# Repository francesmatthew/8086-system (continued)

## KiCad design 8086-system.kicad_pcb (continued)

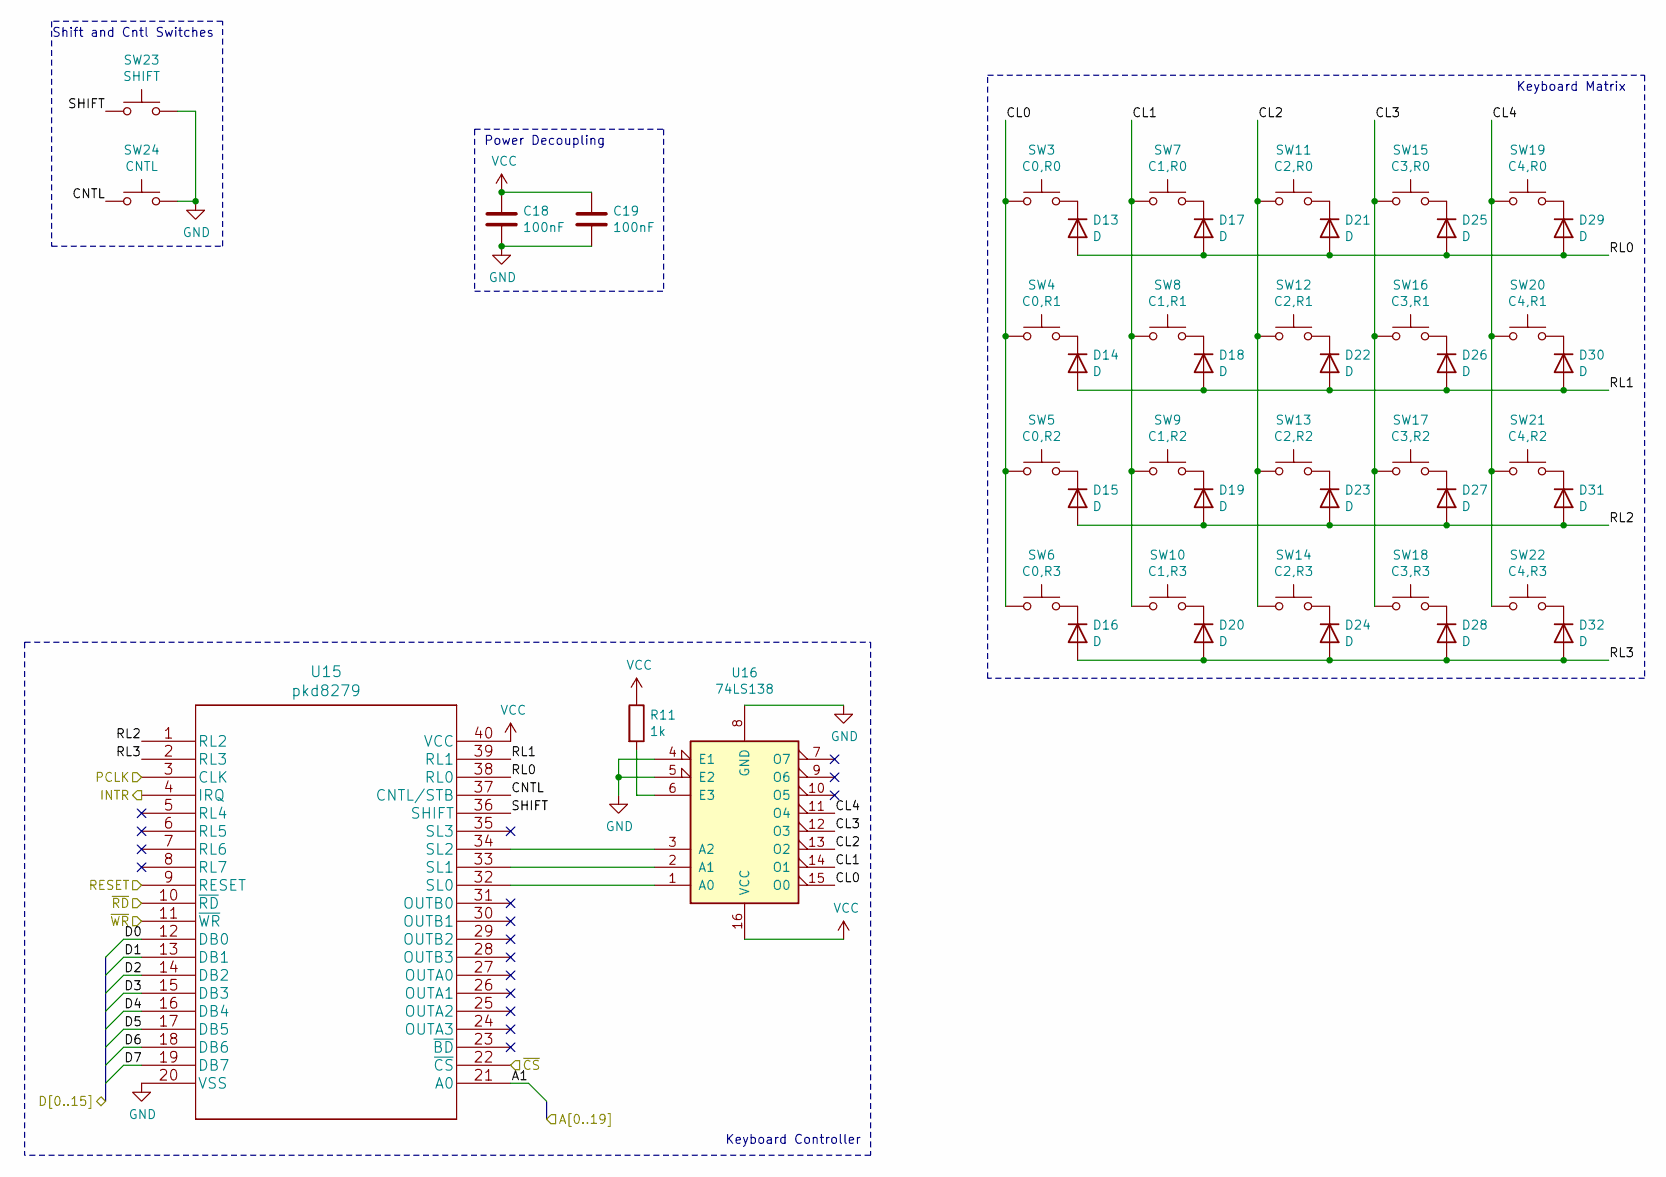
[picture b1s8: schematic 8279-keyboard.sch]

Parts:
C18, C19: 100nF; C_Rect_L4.0mm_W2.5mm_P2.50mm
D13, D14, D15, D16, D17, D18, D19, D20, D21, D22, D23, D24, D25, D26, D27, D28, D29, D30, D31, D32: D; D_DO-35_SOD27_P7.62mm_Horizontal
R11: 1k; R_Axial_DIN0207_L6.3mm_D2.5mm_P10.16mm_Horizontal
SW3: C0,R0; SW_Cherry_MX_1.00u_PCB
SW4: C0,R1; SW_Cherry_MX_1.00u_PCB
SW5: C0,R2; SW_Cherry_MX_1.00u_PCB
SW6: C0,R3; SW_Cherry_MX_1.00u_PCB
SW7: C1,R0; SW_Cherry_MX_1.00u_PCB
SW8: C1,R1; SW_Cherry_MX_1.00u_PCB
SW9: C1,R2; SW_Cherry_MX_1.00u_PCB
SW10: C1,R3; SW_Cherry_MX_1.00u_PCB
SW11: C2,R0; SW_Cherry_MX_1.00u_PCB
SW12: C2,R1; SW_Cherry_MX_1.00u_PCB
SW13: C2,R2; SW_Cherry_MX_1.00u_PCB
SW14: C2,R3; SW_Cherry_MX_1.00u_PCB
SW15: C3,R0; SW_Cherry_MX_1.00u_PCB
SW16: C3,R1; SW_Cherry_MX_1.00u_PCB
SW17: C3,R2; SW_Cherry_MX_1.00u_PCB
SW18: C3,R3; SW_Cherry_MX_1.00u_PCB
SW19: C4,R0; SW_Cherry_MX_1.00u_PCB
SW20: C4,R1; SW_Cherry_MX_1.00u_PCB
SW21: C4,R2; SW_Cherry_MX_1.00u_PCB
SW22: C4,R3; SW_Cherry_MX_1.00u_PCB
SW23: SHIFT; SW_Cherry_MX_1.00u_PCB
SW24: CNTL; SW_Cherry_MX_1.00u_PCB
U15: pkd8279
U16: 74LS138; DIP-16_W7.62mm

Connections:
/8086-processor/A1: U15.21 (A0); also elsewhere on the board
/8086-processor/D0: U15.12 (DB0); also elsewhere on the board
/8086-processor/D1: U15.13 (DB1); also elsewhere on the board
/8086-processor/D2: U15.14 (DB2); also elsewhere on the board
/8086-processor/D3: U15.15 (DB3); also elsewhere on the board
/8086-processor/D4: U15.16 (DB4); also elsewhere on the board
/8086-processor/D5: U15.17 (DB5); also elsewhere on the board
/8086-processor/D6: U15.18 (DB6); also elsewhere on the board
/8086-processor/D7: U15.19 (DB7); also elsewhere on the board
/8279-keyboard/CL0: SW3.1, SW4.1, SW5.1, SW6.1, U16.15 (O0)
/8279-keyboard/CL1: SW7.1, SW8.1, SW9.1, SW10.1, U16.14 (O1)
/8279-keyboard/CL2: SW11.1, SW12.1, SW13.1, SW14.1, U16.13 (O2)
/8279-keyboard/CL3: SW15.1, SW16.1, SW17.1, SW18.1, U16.12 (O3)
/8279-keyboard/CL4: SW19.1, SW20.1, SW21.1, SW22.1, U16.11 (O4)
/8279-keyboard/CNTL: SW24.1, U15.37 (CNTL/STB)
/8279-keyboard/RL0: D13.2 (A), D17.2 (A), D21.2 (A), D25.2 (A), D29.2 (A), U15.38 (RL0)
/8279-keyboard/RL1: D14.2 (A), D18.2 (A), D22.2 (A), D26.2 (A), D30.2 (A), U15.39 (RL1)
/8279-keyboard/RL2: D15.2 (A), D19.2 (A), D23.2 (A), D27.2 (A), D31.2 (A), U15.1 (RL2)
/8279-keyboard/RL3: D16.2 (A), D20.2 (A), D24.2 (A), D28.2 (A), D32.2 (A), U15.2 (RL3)
/8279-keyboard/SHIFT: SW23.1, U15.36 (SHIFT)
/KEYBOARD_INTR: U15.4 (IRQ); also elsewhere on the board
/PCLK: U15.3 (CLK); also elsewhere on the board
/RESET: U15.9 (RESET); also elsewhere on the board
/~CS_KEYBOARD: U15.22 (~CS); also elsewhere on the board
/~RD: U15.10 (~RD); also elsewhere on the board
/~WR: U15.11 (~WR); also elsewhere on the board
GND: C18.2, C19.2, SW23.2, SW24.2, U15.20 (VSS), U16.4 (E1), U16.5 (E2), U16.8 (GND); also elsewhere on the board
unnamed: D13.1 (K), SW3.2
unnamed: D14.1 (K), SW4.2
unnamed: D15.1 (K), SW5.2
unnamed: D16.1 (K), SW6.2
unnamed: D17.1 (K), SW7.2
unnamed: D18.1 (K), SW8.2
unnamed: D19.1 (K), SW9.2
unnamed: D20.1 (K), SW10.2
unnamed: D21.1 (K), SW11.2
unnamed: D22.1 (K), SW12.2
unnamed: D23.1 (K), SW13.2
unnamed: D24.1 (K), SW14.2
unnamed: D25.1 (K), SW15.2
unnamed: D26.1 (K), SW16.2
unnamed: D27.1 (K), SW17.2
unnamed: D28.1 (K), SW18.2
unnamed: D29.1 (K), SW19.2
unnamed: D30.1 (K), SW20.2
unnamed: D31.1 (K), SW21.2
unnamed: D32.1 (K), SW22.2
unnamed: R11.2, U16.6 (E3)
unnamed: U15.32 (SL0), U16.1 (A0)
unnamed: U15.33 (SL1), U16.2 (A1)
unnamed: U15.34 (SL2), U16.3 (A2)
VCC: C18.1, C19.1, R11.1, U15.40 (VCC), U16.16 (VCC); also elsewhere on the board

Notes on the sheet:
Keyboard Matrix
Keyboard Controller
Shift and Cntl Switches
Power Decoupling

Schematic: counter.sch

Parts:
C20: 100nF; C_Rect_L4.0mm_W2.5mm_P2.50mm
J17: Counter0; PinHeader_1x03_P2.54mm_Vertical
J18: Counter1; PinHeader_1x03_P2.54mm_Vertical
J19: Counter2; PinHeader_1x03_P2.54mm_Vertical
R12, R13, R14, R15, R16, R17: 1k; R_Axial_DIN0207_L6.3mm_D2.5mm_P10.16mm_Horizontal
U17: 8254; DIP-24_W15.24mm

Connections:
/8086-processor/A1: U17.19 (A0); also elsewhere on the board
/8086-processor/A2: U17.20 (A1); also elsewhere on the board
/8086-processor/D0: U17.8 (D0); also elsewhere on the board
/8086-processor/D1: U17.7 (D1); also elsewhere on the board
/8086-processor/D2: U17.6 (D2); also elsewhere on the board
/8086-processor/D3: U17.5 (D3); also elsewhere on the board
/8086-processor/D4: U17.4 (D4); also elsewhere on the board
/8086-processor/D5: U17.3 (D5); also elsewhere on the board
/8086-processor/D6: U17.2 (D6); also elsewhere on the board
/8086-processor/D7: U17.1 (D7); also elsewhere on the board
/COUNTER_INTR: U17.13 (OUT1); also elsewhere on the board
/~CS_COUNTER: U17.21 (~CS~); also elsewhere on the board
/~RD: U17.22 (~RD~); also elsewhere on the board
/~WR: U17.23 (~WR~); also elsewhere on the board
GND: C20.2, J18.3, R12.2, R13.2, R14.2, R15.2, R16.2, R17.2, U17.12 (GND); also elsewhere on the board
unnamed: J17.1, R12.1, U17.9 (CLK0)
unnamed: J17.2, R13.1, U17.11 (G0)
unnamed: J17.3, U17.10 (OUT0)
unnamed: J18.1, R14.1, U17.15 (CLK1)
unnamed: J18.2, R15.1, U17.14 (G1)
unnamed: J19.1, R16.1, U17.18 (CLK2)
unnamed: J19.2, R17.1, U17.16 (G2)
unnamed: J19.3, U17.17 (OUT2)
VCC: C20.1, U17.24 (VCC); also elsewhere on the board

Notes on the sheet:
8254 Interval Timer
Power decoupling

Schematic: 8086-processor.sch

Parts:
C21, C22, C23, C24, C25, C26, C27, C28: 100nF; C_Rect_L4.0mm_W2.5mm_P2.50mm
D3: 1N4148; D_DO-35_SOD27_P7.62mm_Horizontal
R18, R20: 1k; R_Axial_DIN0207_L6.3mm_D2.5mm_P10.16mm_Horizontal
R19: 10k; R_Axial_DIN0207_L6.3mm_D2.5mm_P10.16mm_Horizontal
SW25: NMI; SW_Cherry_MX_1.00u_PCB
U18: 8086_Min_Mode; DIP-40_W15.24mm
U19, U21, U22: 74LS374; DIP-20_W7.62mm
U20: 74LS244; DIP-20_W7.62mm
U23, U24: 74LS245; DIP-20_W7.62mm

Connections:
/8086-processor/A0: U19.9 (O3); also elsewhere on the board
/8086-processor/A1: U19.6 (O2); also elsewhere on the board
/8086-processor/A2: U19.5 (O1); also elsewhere on the board
/8086-processor/A3: U19.2 (O0); also elsewhere on the board
/8086-processor/A4: U19.12 (O4); also elsewhere on the board
/8086-processor/A5: U19.15 (O5); also elsewhere on the board
/8086-processor/A6: U19.16 (O6); also elsewhere on the board
/8086-processor/A7: U19.19 (O7); also elsewhere on the board
/8086-processor/A8: U21.9 (O3); also elsewhere on the board
/8086-processor/A9: U21.6 (O2); also elsewhere on the board
/8086-processor/A10: U21.5 (O1); also elsewhere on the board
/8086-processor/A11: U21.2 (O0); also elsewhere on the board
/8086-processor/A12: U21.12 (O4); also elsewhere on the board
/8086-processor/A13: U21.15 (O5); also elsewhere on the board
/8086-processor/A14: U21.16 (O6); also elsewhere on the board
/8086-processor/A15: U21.19 (O7); also elsewhere on the board
/8086-processor/A16: U22.2 (O0); also elsewhere on the board
/8086-processor/A17: U22.5 (O1); also elsewhere on the board
/8086-processor/A18: U22.6 (O2); also elsewhere on the board
/8086-processor/A19: U22.9 (O3); also elsewhere on the board
/8086-processor/ALE: U18.25 (ALE), U19.11 (Cp), U21.11 (Cp), U22.11 (Cp)
/8086-processor/D0: U23.18 (B0); also elsewhere on the board
/8086-processor/D1: U23.17 (B1); also elsewhere on the board
/8086-processor/D2: U23.16 (B2); also elsewhere on the board
/8086-processor/D3: U23.15 (B3); also elsewhere on the board
/8086-processor/D4: U23.14 (B4); also elsewhere on the board
/8086-processor/D5: U23.13 (B5); also elsewhere on the board
/8086-processor/D6: U23.12 (B6); also elsewhere on the board
/8086-processor/D7: U23.11 (B7); also elsewhere on the board
/8086-processor/D8: U24.18 (B0); also elsewhere on the board
/8086-processor/D9: U24.17 (B1); also elsewhere on the board
/8086-processor/D10: U24.16 (B2); also elsewhere on the board
/8086-processor/D11: U24.15 (B3); also elsewhere on the board
/8086-processor/D12: U24.14 (B4); also elsewhere on the board
/8086-processor/D13: U24.13 (B5); also elsewhere on the board
/8086-processor/D14: U24.12 (B6); also elsewhere on the board
/8086-processor/D15: U24.11 (B7); also elsewhere on the board
/8086-processor/DT\~R: U18.27 (DT/~R~), U23.1 (A->B), U24.1 (A->B)
/8086-processor/NMI: U18.17 (NMI), U20.12 (O3a)
/8086-processor/~DEN: U18.26 (~DEN~), U23.19 (CE), U24.19 (CE)
/CLK: U18.19 (CLK); also elsewhere on the board
/INTR: U18.18 (INTR); also elsewhere on the board
/M\~IO: U20.18 (O0a); also elsewhere on the board
/READY: U18.22 (READY); also elsewhere on the board
/RESET: U18.21 (RESET); also elsewhere on the board
/~BHE: U22.12 (O4); also elsewhere on the board
/~INTA: U18.24 (~INTA~); also elsewhere on the board
/~RD: U20.14 (O2a); also elsewhere on the board
/~WR: U20.16 (O1a); also elsewhere on the board
GND: C22.1, C23.1, C24.1, C25.1, C26.1, C27.1, C28.1, R19.1, U18.1 (GND), U18.20 (GND), U18.23 (~TEST~), U18.31 (HOLD), U19.1 (OE), U19.10 (GND), U20.1 (OEa), U20.10 (GND), U20.11 (I0b), U20.13 (I1b), U20.15 (I2b), U20.17 (I3b), U20.19 (OEb), U21.1 (OE), U21.10 (GND), U22.1 (OE), U22.10 (GND), U22.14 (D5), U22.17 (D6), U22.18 (D7), U23.10 (GND), U24.10 (GND); also elsewhere on the board
unnamed: C21.2, D3.2 (A), R20.1, U20.8 (I3a)
unnamed: D3.1 (K), R19.2, R20.2, SW25.1
unnamed: R18.2, U18.33 (MN/~MX~)
unnamed: U18.2 (AD14), U21.17 (D6), U24.8 (A6)
unnamed: U18.3 (AD13), U21.14 (D5), U24.7 (A5)
unnamed: U18.4 (AD12), U21.13 (D4), U24.6 (A4)
unnamed: U18.5 (AD11), U21.3 (D0), U24.5 (A3)
unnamed: U18.6 (AD10), U21.4 (D1), U24.4 (A2)
unnamed: U18.7 (AD9), U21.7 (D2), U24.3 (A1)
unnamed: U18.8 (AD8), U21.8 (D3), U24.2 (A0)
unnamed: U18.9 (AD7), U19.18 (D7), U23.9 (A7)
unnamed: U18.10 (AD6), U19.17 (D6), U23.8 (A6)
unnamed: U18.11 (AD5), U19.14 (D5), U23.7 (A5)
unnamed: U18.12 (AD4), U19.13 (D4), U23.6 (A4)
unnamed: U18.13 (AD3), U19.3 (D0), U23.5 (A3)
unnamed: U18.14 (AD2), U19.4 (D1), U23.4 (A2)
unnamed: U18.15 (AD1), U19.7 (D2), U23.3 (A1)
unnamed: U18.16 (AD0), U19.8 (D3), U23.2 (A0)
unnamed: U18.28 (M/~IO~), U20.2 (I0a)
unnamed: U18.29 (~WR~), U20.4 (I1a)
unnamed: U18.32 (~RD~), U20.6 (I2a)
unnamed: U18.34 (~BHE~/S7), U22.13 (D4)
unnamed: U18.35 (A19/S6), U22.8 (D3)
unnamed: U18.36 (A18/S5), U22.7 (D2)
unnamed: U18.37 (A17/S4), U22.4 (D1)
unnamed: U18.38 (A16/S3), U22.3 (D0)
unnamed: U18.39 (AD15), U21.18 (D7), U24.9 (A7)
VCC: C21.1, C22.2, C23.2, C24.2, C25.2, C26.2, C27.2, C28.2, R18.1, SW25.2, U18.40 (VCC), U19.20 (VCC), U20.20 (VCC), U21.20 (VCC), U22.20 (VCC), U23.20 (VCC), U24.20 (VCC); also elsewhere on the board

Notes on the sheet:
Data Bus Transceivers
Address Bus Latches
8086 Processor
Power Decoupling
Non-Maskable Interrupt Button

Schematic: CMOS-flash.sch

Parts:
C29, C30, C31, C32, C33, C34: 100nF; C_Rect_L4.0mm_W2.5mm_P2.50mm
U25, U26: 74LS138; DIP-16_W7.62mm
U27, U28: 28F010

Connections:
+12V: C29.1, C30.1, U27.1 (VPP), U28.1 (VPP); also elsewhere on the board
/8086-processor/A0: U26.5 (E2); also elsewhere on the board
/8086-processor/A1: U27.12 (A0), U28.12 (A0); also elsewhere on the board
/8086-processor/A2: U27.11 (A1), U28.11 (A1); also elsewhere on the board
/8086-processor/A3: U27.10 (A2), U28.10 (A2); also elsewhere on the board
/8086-processor/A4: U27.9 (A3), U28.9 (A3); also elsewhere on the board
/8086-processor/A5: U27.8 (A4), U28.8 (A4); also elsewhere on the board
/8086-processor/A6: U27.7 (A5), U28.7 (A5); also elsewhere on the board
/8086-processor/A7: U27.6 (A6), U28.6 (A6); also elsewhere on the board
/8086-processor/A8: U27.5 (A7), U28.5 (A7); also elsewhere on the board
/8086-processor/A9: U27.27 (A8), U28.27 (A8); also elsewhere on the board
/8086-processor/A10: U27.26 (A9), U28.26 (A9); also elsewhere on the board
/8086-processor/A11: U27.23 (A10), U28.23 (A10); also elsewhere on the board
/8086-processor/A12: U27.25 (A11), U28.25 (A11); also elsewhere on the board
/8086-processor/A13: U27.4 (A12), U28.4 (A12); also elsewhere on the board
/8086-processor/A14: U27.28 (A13), U28.28 (A13); also elsewhere on the board
/8086-processor/A15: U27.29 (A14), U28.29 (A14); also elsewhere on the board
/8086-processor/A16: U27.3 (A15), U28.3 (A15); also elsewhere on the board
/8086-processor/A17: U27.2 (A16), U28.2 (A16); also elsewhere on the board
/8086-processor/A18: U25.1 (A0), U26.1 (A0); also elsewhere on the board
/8086-processor/A19: U25.2 (A1), U26.2 (A1); also elsewhere on the board
/8086-processor/D0: U28.13 (DQ0); also elsewhere on the board
/8086-processor/D1: U28.14 (DQ1); also elsewhere on the board
/8086-processor/D2: U28.15 (DQ2); also elsewhere on the board
/8086-processor/D3: U28.17 (DQ3); also elsewhere on the board
/8086-processor/D4: U28.18 (DQ4); also elsewhere on the board
/8086-processor/D5: U28.19 (DQ5); also elsewhere on the board
/8086-processor/D6: U28.20 (DQ6); also elsewhere on the board
/8086-processor/D7: U28.21 (DQ7); also elsewhere on the board
/8086-processor/D8: U27.13 (DQ0); also elsewhere on the board
/8086-processor/D9: U27.14 (DQ1); also elsewhere on the board
/8086-processor/D10: U27.15 (DQ2); also elsewhere on the board
/8086-processor/D11: U27.17 (DQ3); also elsewhere on the board
/8086-processor/D12: U27.18 (DQ4); also elsewhere on the board
/8086-processor/D13: U27.19 (DQ5); also elsewhere on the board
/8086-processor/D14: U27.20 (DQ6); also elsewhere on the board
/8086-processor/D15: U27.21 (DQ7); also elsewhere on the board
/CMOS-flash/~CE_HI_BYTE: U25.12 (O3), U27.22 (CE)
/CMOS-flash/~CE_LOW_BYTE: U26.12 (O3), U28.22 (CE)
/M\~IO: U25.6 (E3), U26.6 (E3); also elsewhere on the board
/~BHE: U25.5 (E2); also elsewhere on the board
/~RD: U27.24 (OE), U28.24 (OE); also elsewhere on the board
/~WR: U27.31 (WE), U28.31 (WE); also elsewhere on the board
GND: C29.2, C30.2, C31.2, C32.2, C33.2, C34.2, U25.3 (A2), U25.4 (E1), U25.8 (GND), U26.3 (A2), U26.4 (E1), U26.8 (GND), U27.16 (VSS), U28.16 (VSS); also elsewhere on the board
VCC: C31.1, C32.1, C33.1, C34.1, U25.16 (VCC), U26.16 (VCC), U27.32 (VCC), U28.32 (VCC); also elsewhere on the board

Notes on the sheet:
256kB CMOS Flash Addresses 0xC0000 to 0xFFFFF
Address Decoding
Power Decoupling
Flash Memory Chips

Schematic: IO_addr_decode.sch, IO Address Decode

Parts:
C35, C36: 100nF; C_Rect_L4.0mm_W2.5mm_P2.50mm
U29: 74LS30; DIP-14_W7.62mm
U30, U31: PAL16L8; DIP-20_W7.62mm

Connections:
/8086-processor/A0: U30.1 (I1), U31.1 (I1); also elsewhere on the board
/8086-processor/A1: U30.2 (I2), U31.2 (I2); also elsewhere on the board
/8086-processor/A2: U30.3 (I3), U31.3 (I3); also elsewhere on the board
/8086-processor/A3: U30.4 (I4), U31.4 (I4); also elsewhere on the board
/8086-processor/A4: U30.5 (I5), U31.5 (I5); also elsewhere on the board
/8086-processor/A5: U30.6 (I6), U31.6 (I6); also elsewhere on the board
/8086-processor/A6: U30.7 (I7), U31.7 (I7); also elsewhere on the board
/8086-processor/A7: U30.8 (I8), U31.8 (I8); also elsewhere on the board
/8086-processor/A8: U29.1; also elsewhere on the board
/8086-processor/A9: U29.2; also elsewhere on the board
/8086-processor/A10: U29.3; also elsewhere on the board
/8086-processor/A11: U29.4; also elsewhere on the board
/8086-processor/A12: U29.5; also elsewhere on the board
/8086-processor/A13: U29.6; also elsewhere on the board
/8086-processor/A14: U29.11; also elsewhere on the board
/8086-processor/A15: U29.12; also elsewhere on the board
/IO_addr_decode/~HI_BYTE_FF: U29.8, U30.9 (I9), U31.9 (I9)
/M\~IO: U30.11 (I10), U31.11 (I10); also elsewhere on the board
/~BHE: U30.12 (IO8), U31.12 (IO8); also elsewhere on the board
/~CS_COUNTER: U30.15 (IO5); also elsewhere on the board
/~CS_INTR: U30.16 (IO4); also elsewhere on the board
/~CS_KEYBOARD: U30.14 (IO6); also elsewhere on the board
/~CS_PPI1: U30.18 (IO2); also elsewhere on the board
/~CS_PPI2: U30.19 (IO1); also elsewhere on the board
/~CS_PPI3: U30.17 (I03); also elsewhere on the board
/~CS_UART: U31.14 (IO6); also elsewhere on the board
/~DIP_CS: U31.16 (IO4); also elsewhere on the board
/~EVEN_7_SEG_CS: U31.18 (IO2); also elsewhere on the board
/~LCD_CS: U31.15 (IO5); also elsewhere on the board
/~LED_CS: U31.19 (IO1); also elsewhere on the board
/~ODD_7_SEG_CS: U31.17 (I03); also elsewhere on the board
GND: C35.2, C36.2, U29.7 (GND), U30.10 (GND), U31.10 (GND); also elsewhere on the board
VCC: C35.1, C36.1, U29.14 (VCC), U30.20 (VCC), U31.20 (VCC); also elsewhere on the board

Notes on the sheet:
Decode high byte
Power decoupling
16L8 PAL: decode low byte

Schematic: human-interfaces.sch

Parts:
C37, C38, C39, C40, C41: 100nF; C_Rect_L4.0mm_W2.5mm_P2.50mm
D4, D5, D6, D7, D8, D9, D10, D11: LED; LED_D5.0mm
DS1: LCD4x20; Mouser Part Number 763-0420AZFLYBW33V3
R21, R22: R; R_Axial_DIN0207_L6.3mm_D2.5mm_P10.16mm_Horizontal
RN1, RN2: R_Pack08; DIP-16_W7.62mm
SW26: SW_DIP_x08; DIP-16_W7.62mm
U32: 74LS02; DIP-20_W7.62mm
U33: 74LS32; DIP-20_W7.62mm
U34, U36, U38: 74LS374; DIP-20_W7.62mm
U37, U40: HDSP-A153; HDSP-A151
U39: 74LS244; DIP-20_W7.62mm

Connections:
/8086-processor/A1: DS1.5 (R/W); also elsewhere on the board
/8086-processor/A2: DS1.4 (RS); also elsewhere on the board
/8086-processor/D0: DS1.7 (DB0), U34.3 (D0), U36.3 (D0), U39.18 (O0a); also elsewhere on the board
/8086-processor/D1: DS1.8 (DB1), U34.4 (D1), U36.4 (D1), U39.16 (O1a); also elsewhere on the board
/8086-processor/D2: DS1.9 (DB2), U34.7 (D2), U36.7 (D2), U39.14 (O2a); also elsewhere on the board
/8086-processor/D3: DS1.10 (DB3), U34.8 (D3), U36.8 (D3), U39.12 (O3a); also elsewhere on the board
/8086-processor/D4: DS1.11 (DB4), U34.13 (D4), U36.13 (D4), U39.9 (O0b); also elsewhere on the board
/8086-processor/D5: DS1.12 (DB5), U34.14 (D5), U36.14 (D5), U39.7 (O1b); also elsewhere on the board
/8086-processor/D6: DS1.13 (DB6), U34.17 (D6), U36.17 (D6), U39.5 (O2b); also elsewhere on the board
/8086-processor/D7: DS1.14 (DB7), U34.18 (D7), U36.18 (D7), U39.3 (O3b); also elsewhere on the board
/8086-processor/D8: U38.3 (D0); also elsewhere on the board
/8086-processor/D9: U38.4 (D1); also elsewhere on the board
/8086-processor/D10: U38.7 (D2); also elsewhere on the board
/8086-processor/D11: U38.8 (D3); also elsewhere on the board
/8086-processor/D12: U38.13 (D4); also elsewhere on the board
/8086-processor/D13: U38.14 (D5); also elsewhere on the board
/8086-processor/D14: U38.17 (D6); also elsewhere on the board
/8086-processor/D15: U38.18 (D7); also elsewhere on the board
/human-interfaces/V0: DS1.3 (V0), R21.2, R22.1
/~DIP_CS: U33.1; also elsewhere on the board
/~EVEN_7_SEG_CS: U32.5; also elsewhere on the board
/~LCD_CS: U32.11; also elsewhere on the board
/~LED_CS: U32.2; also elsewhere on the board
/~ODD_7_SEG_CS: U32.8; also elsewhere on the board
/~RD: U33.2; also elsewhere on the board
/~WR: U32.3, U32.6, U32.9, U32.12; also elsewhere on the board
GND: C37.2, C38.2, C39.2, C40.2, C41.2, DS1.1 (VSS), DS1.MH1, DS1.MH2, DS1.MH3, DS1.MH4, R22.2, SW26.1, SW26.2, SW26.3, SW26.4, SW26.5, SW26.6, SW26.7, SW26.8, U32.7 (GND), U33.4, U33.5, U33.7 (GND), U33.9, U33.10, U33.12, U33.13, U34.1 (OE), U34.10 (GND), U36.1 (OE), U36.10 (GND), U37.1 (CC), U37.6 (CC), U38.1 (OE), U38.10 (GND), U39.10 (GND), U40.1 (CC), U40.6 (CC); also elsewhere on the board
unnamed: D4.1 (K), RN1.16 (R1.2)
unnamed: D5.1 (K), RN1.15 (R2.2)
unnamed: D6.1 (K), RN1.14 (R3.2)
unnamed: D7.1 (K), RN1.13 (R4.2)
unnamed: D8.1 (K), RN1.12 (R5.2)
unnamed: D9.1 (K), RN1.11 (R6.2)
unnamed: D10.1 (K), RN1.10 (R7.2)
unnamed: D11.1 (K), RN1.9 (R8.2)
unnamed: DS1.6 (E), U32.13
unnamed: RN1.1 (R1.1), U34.2 (O0)
unnamed: RN1.2 (R2.1), U34.5 (O1)
unnamed: RN1.3 (R3.1), U34.6 (O2)
unnamed: RN1.4 (R4.1), U34.9 (O3)
unnamed: RN1.5 (R5.1), U34.12 (O4)
unnamed: RN1.6 (R6.1), U34.15 (O5)
unnamed: RN1.7 (R7.1), U34.16 (O6)
unnamed: RN1.8 (R8.1), U34.19 (O7)
unnamed: RN2.9 (R8.2), SW26.16, U39.2 (I0a)
unnamed: RN2.10 (R7.2), SW26.15, U39.4 (I1a)
unnamed: RN2.11 (R6.2), SW26.14, U39.6 (I2a)
unnamed: RN2.12 (R5.2), SW26.13, U39.8 (I3a)
unnamed: RN2.13 (R4.2), SW26.12, U39.11 (I0b)
unnamed: RN2.14 (R3.2), SW26.11, U39.13 (I1b)
unnamed: RN2.15 (R2.2), SW26.10, U39.15 (I2b)
unnamed: RN2.16 (R1.2), SW26.9, U39.17 (I3b)
unnamed: U32.1, U34.11 (Cp)
unnamed: U32.4, U36.11 (Cp)
unnamed: U32.10, U38.11 (Cp)
unnamed: U33.3, U39.1 (OEa), U39.19 (OEb)
unnamed: U36.2 (O0), U37.7 (DP)
unnamed: U36.5 (O1), U37.3 (G)
unnamed: U36.6 (O2), U37.2 (F)
unnamed: U36.9 (O3), U37.4 (E)
unnamed: U36.12 (O4), U37.5 (D)
unnamed: U36.15 (O5), U37.8 (C)
unnamed: U36.16 (O6), U37.9 (B)
unnamed: U36.19 (O7), U37.10 (A)
unnamed: U38.2 (O0), U40.7 (DP)
unnamed: U38.5 (O1), U40.3 (G)
unnamed: U38.6 (O2), U40.2 (F)
unnamed: U38.9 (O3), U40.4 (E)
unnamed: U38.12 (O4), U40.5 (D)
unnamed: U38.15 (O5), U40.8 (C)
unnamed: U38.16 (O6), U40.9 (B)
unnamed: U38.19 (O7), U40.10 (A)
VCC: C37.1, C38.1, C39.1, C40.1, C41.1, D4.2 (A), D5.2 (A), D6.2 (A), D7.2 (A), D8.2 (A), D9.2 (A), D10.2 (A), D11.2 (A), DS1.2 (VDD), R21.1, RN2.1 (R1.1), RN2.2 (R2.1), RN2.3 (R3.1), RN2.4 (R4.1), RN2.5 (R5.1), RN2.6 (R6.1), RN2.7 (R7.1), RN2.8 (R8.1), U32.14 (VCC), U33.14 (VCC), U34.20 (VCC), U36.20 (VCC), U38.20 (VCC), U39.20 (VCC); also elsewhere on the board

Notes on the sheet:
Power Decoupling
4x20 LCD Display 0xFFD0, 0xFFD2, 0xFFD4, 0xFFD6
8 LEDs 0xFFCC
Unused Gates
DIP Switches 0xFFCA
7-Segment Display 0xFFCE, 0xFFCF

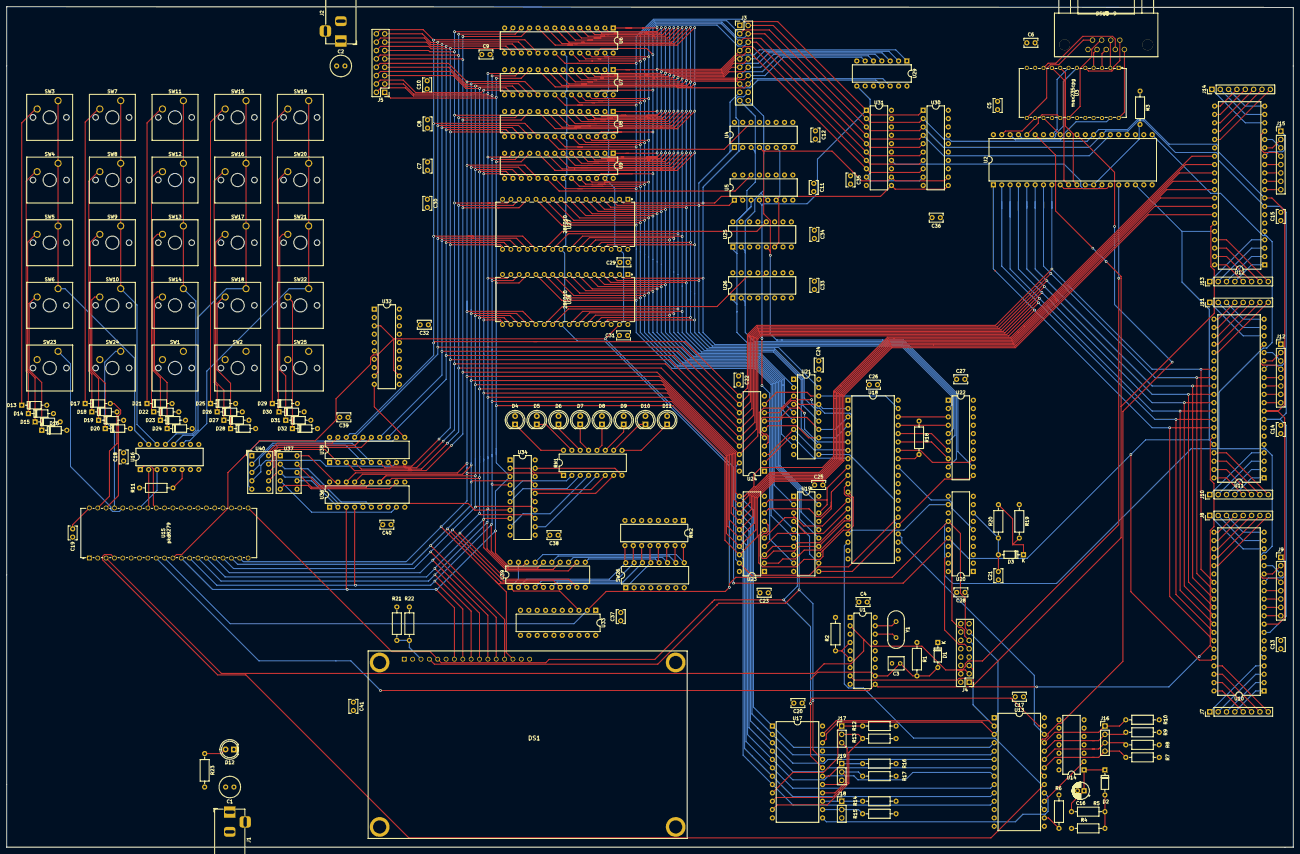
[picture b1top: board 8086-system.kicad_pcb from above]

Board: 4 copper layers, 391.2 x 255.5 mm, 184 parts (0 on the bottom side), 294 nets.

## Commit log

2021-11-12 Inital commit/added requesite libraries
2021-11-14 created 8086 processor block | created external connectors block
2021-11-15 created 8284A clock generator block
2021-11-28 created 28F010 CMOS flash block; improved power decoupling; added M/~IO pin from 8086 sheet; reduced no. of logic gates in 8086 processor block; added +12V; moved input power to external-connectors s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
2021-11-29 created 16550 UART interface block
2021-11-29 use more common type of switch for nmi
2021-11-30 fixed MWTC MRDC IOWC IORC decoding
2021-12-01 Add SRAM and PPIs
2021-12-01 added 8279 keyboard block
2021-12-01 Replaced MWTC MRDC IOWC IORC with WR RD; buffered control bus; consolidated logic gates
2021-12-02 Fix high/low byte on PPIs; Add counter and interrupt controller
2021-12-02 Untrack 8086-system-cache.lib
2021-12-02 Fix disconnected WR/RD on PPIs
2021-12-02 Debounce pushbutton for 8259
2021-12-03 IO address decoding
2021-12-03 created human interface I/O devices
2021-12-03 Fix wiring in root sheet
2021-12-04 Decode BHE for IO addresses
2021-12-04 General edits; removed floating inputs
2021-12-04 Updates to pass ERC
2021-12-06 Assign footprints for most symbols
2021-12-06 Assigned footprints
2021-12-08 assign footprints and edits
2021-12-09 begin pcb layout
2021-12-10 Layout PPI, interrupt, counter, and UART blocks
2021-12-13 more traces routed
2021-12-13 Route some more, starting re-doing memory routing
2021-12-13 continued pcb routing
2021-12-13 Route data bus lines, most chip selects
2021-12-14 more pcb routing
2021-12-14 Finished routing
2021-12-14 Minor updates to silkscreen
2021-12-14 refilled fill zones, removed pdf
2021-12-14 add images to README
